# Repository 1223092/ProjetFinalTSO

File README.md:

## Project: Serrebrooke

### Logiciel
#### Comprend les dossiers des fichiers de programmation.

### Manuel Technique
#### Comprend le fichier texte explicant l'entièreté du projet.

### Materiel
#### Comprend de la documentation sur tous les objets physiques utilisé.

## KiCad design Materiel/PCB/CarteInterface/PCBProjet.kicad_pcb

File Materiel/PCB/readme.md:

# Schémas 
Répertoire qui contient fichiers KiCAD de la carte d'extension Serrebrooke.

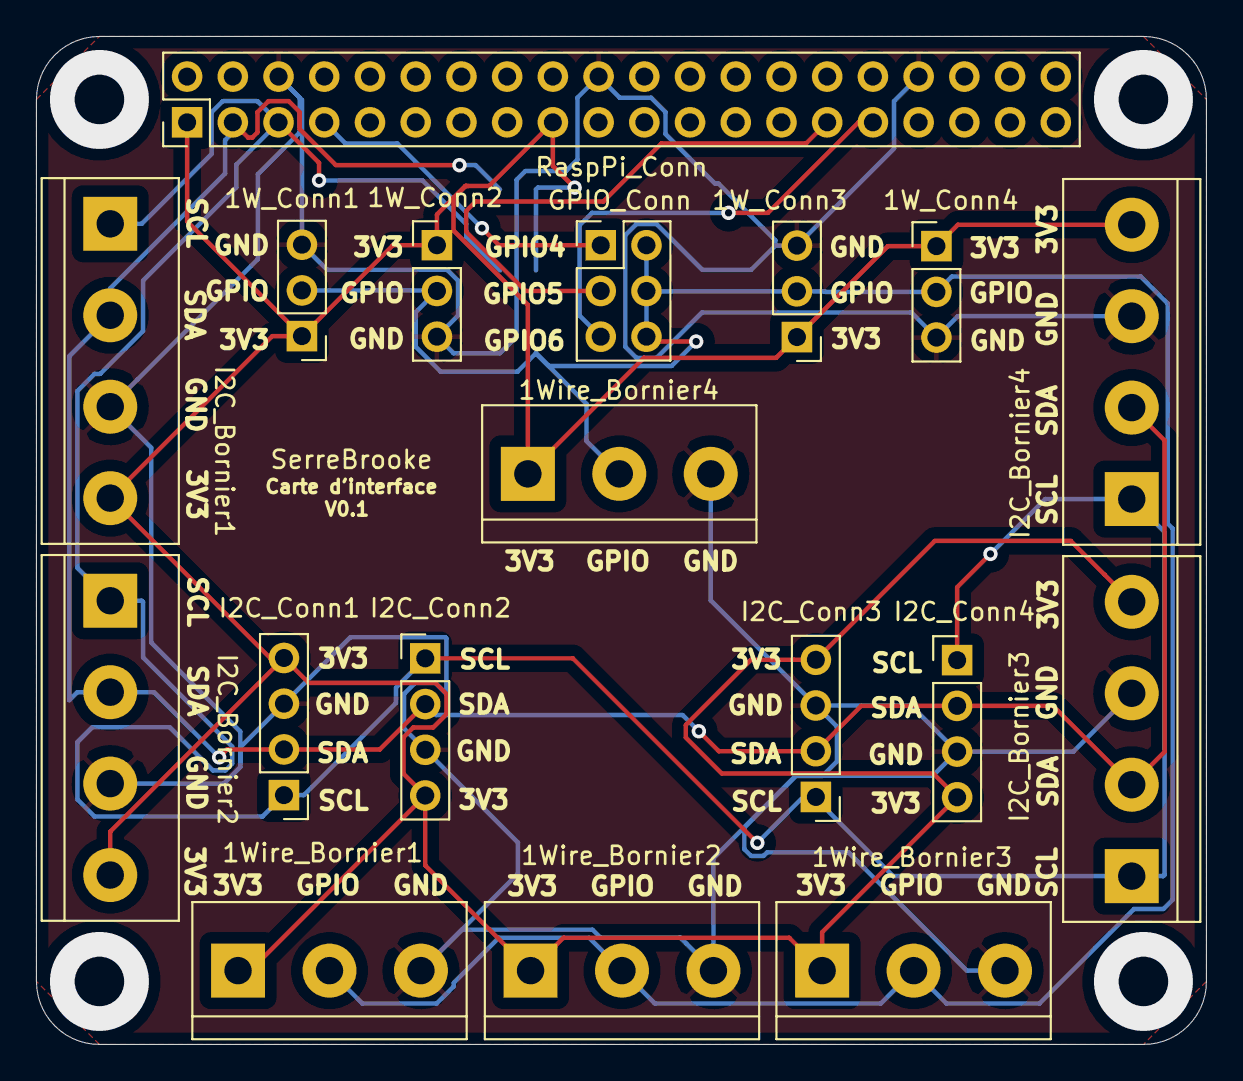
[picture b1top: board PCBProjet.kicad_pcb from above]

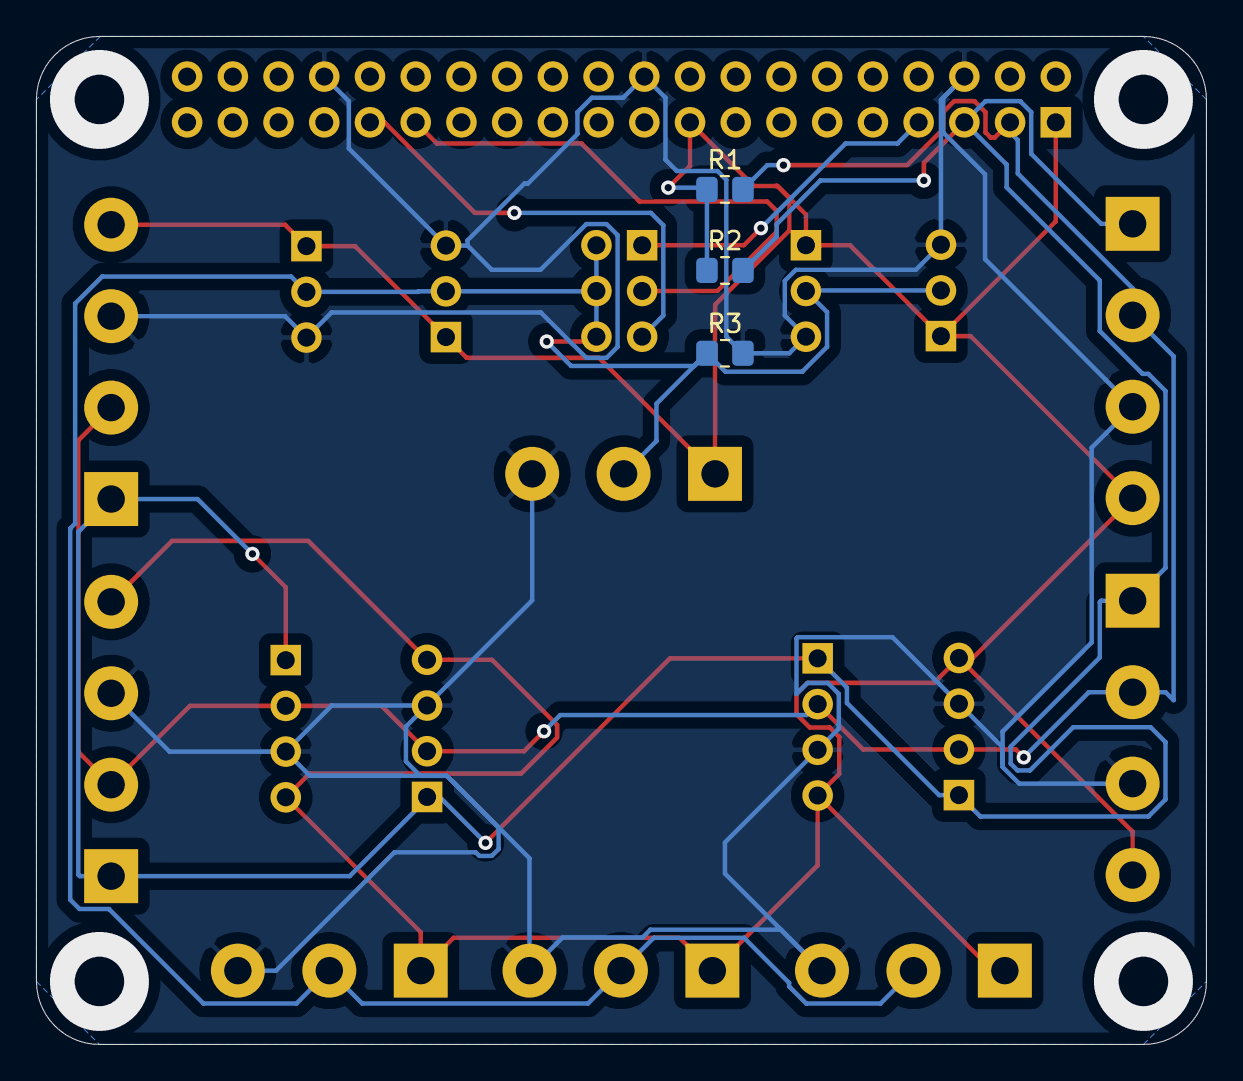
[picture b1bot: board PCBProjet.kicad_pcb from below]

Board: 2 copper layers, 65.0 x 56.0 mm, 21 parts (3 on the bottom side), 8 nets.

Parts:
1W_Conn1, 1W_Conn2, 1W_Conn3, 1W_Conn4: Conn_01x03; PinHeader_1x03_P2.54mm_Vertical
1Wire_Bornier1, 1Wire_Bornier2, 1Wire_Bornier3, 1Wire_Bornier4: Screw_Terminal_01x03; TerminalBlock_bornier-3_P5.08mm
GPIO_Conn: Conn_GPIO; PinHeader_2x03_P2.54mm_Vertical
I2C_Bornier1, I2C_Bornier2, I2C_Bornier3, I2C_Bornier4: Screw_Terminal_01x04; TerminalBlock_bornier-4_P5.08mm
I2C_Conn1, I2C_Conn2, I2C_Conn3, I2C_Conn4: Conn_01x04; PinHeader_1x04_P2.54mm_Vertical
R1, R2, R3: 4.7k; R_0805_2012Metric_Pad1.20x1.40mm_HandSolder
RaspPi_Conn: Raspberry_Pi_2_3; PinHeader_2x20_P2.54mm_Vertical

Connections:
/3V3: 1W_Conn1.1, 1W_Conn2.1, 1W_Conn3.1, 1W_Conn4.1, 1Wire_Bornier1.1, 1Wire_Bornier2.1, 1Wire_Bornier3.1, 1Wire_Bornier4.1, I2C_Bornier1.4, I2C_Bornier2.4, I2C_Bornier3.4, I2C_Bornier4.4, I2C_Conn1.4, I2C_Conn2.4, I2C_Conn3.4, I2C_Conn4.4, R1.1, R2.1, RaspPi_Conn.1, RaspPi_Conn.17
/GND: 1W_Conn1.3, 1W_Conn2.3, 1W_Conn3.3, 1W_Conn4.3, 1Wire_Bornier1.3, 1Wire_Bornier2.3, 1Wire_Bornier3.3, 1Wire_Bornier4.3, I2C_Bornier1.3, I2C_Bornier2.3, I2C_Bornier3.3, I2C_Bornier4.3, I2C_Conn1.3, I2C_Conn2.3, I2C_Conn3.3, I2C_Conn4.3, R3.2, RaspPi_Conn.6, RaspPi_Conn.20, RaspPi_Conn.34
/GPIO: 1W_Conn1.2, 1W_Conn2.2, 1W_Conn3.2, 1W_Conn4.2, 1Wire_Bornier1.2, 1Wire_Bornier2.2, 1Wire_Bornier3.2, 1Wire_Bornier4.2, GPIO_Conn.2, GPIO_Conn.4, GPIO_Conn.6, R3.1
/GPIO4: GPIO_Conn.1, RaspPi_Conn.7
/GPIO5: GPIO_Conn.3, RaspPi_Conn.29
/GPIO6: GPIO_Conn.5, RaspPi_Conn.31
/SCL: I2C_Bornier1.1, I2C_Bornier2.1, I2C_Bornier3.1, I2C_Bornier4.1, I2C_Conn1.1, I2C_Conn2.1, I2C_Conn3.1, I2C_Conn4.1, R2.2, RaspPi_Conn.5
/SDA: I2C_Bornier1.2, I2C_Bornier2.2, I2C_Bornier3.2, I2C_Bornier4.2, I2C_Conn1.2, I2C_Conn2.2, I2C_Conn3.2, I2C_Conn4.2, R1.2, RaspPi_Conn.3

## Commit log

2023-11-30 Release Balena
2023-12-19 Update Controle_GPIO.py
    RELEASE
    0.0.0+rev53
    avec boutons de Téléchargement de log: Trois boutons permettant de télécharger le journal des actions au format JSON, XML ou CSV.
2023-12-22 update du README
    ajout du brief de Controle_GPIO.py dans le README
2024-02-12 Test ordi Loic a Github
    One wire réglé.
    Enlevé les parties sur Hydroponie.
    Test interface écran physique.
2024-02-16 Les fichiers de configuration
    Les fichiers de configuration pour Docker et Balena.
    Changement fait pour avoir un point d'accès WIFI .
2024-02-28 Changement du nom du repo
    test changement nom
2024-02-28 Modification de l'arborescence
    test
2024-02-28 Ajout dossier manuel technique
    test1
2024-02-28 changer nom d'un dossier
    test1
2024-02-28 Mise à jour
    test1
2024-02-28 Travailler sur manuel technique
2024-03-13 Ajout affichage
    Ajout du status de connection sur interface
2024-03-13 temps d'acquisition
    changement pour le temps d'acquisition
2024-03-13 Update syst_interface.py
    Oublier d'importé syst_logique
2024-03-15 Affichage du status de connection
    L'écran affiche le status de connection : ON ou OFF
2024-03-18 nettoyage
    effacer les fichiers non necessaire
2024-03-18 version test du site
    version test du site de controle avec flask
2024-03-20 Delete du fichier boucle
    C'était un fichier de test
2024-03-20 Status de connection écran
2024-03-21 site
    nouveau site avec control et interface de programation .
    visuelment plus esthetique
2024-03-22 Update site.py
    ajout d'un sub tab pour programmation de valeurs fixes
2024-03-22 Update site.py
    css pour les text boxes de programmation de valeurs fixes
2024-03-22 Update getSensors_ds18b20.py
    changement pour avoir une tempMOY
2024-03-22 Update site.py
    fonction pour le boutton clear et set de temperature
2024-03-22 Update syst_interface.py
    fix affichage Temp. MOY
2024-04-03 Version présenstation
    version allégé pour la présentation 11 avril
2024-04-03 Mis à la bonne place
2024-04-05 documentation
2024-04-08 Manuel technique
    Description de l'échéancier.
    Grille des cours.
2024-04-10 réglage de bug sur le status de connexion
2024-04-18 Correction boucle de vérif statu connection
2024-04-19 Documentation
    Capteur d'humidité
2024-04-22 Manuel technique
    Procédure pour changer le logicel des prises intelligentes
2024-04-23 Site et boucles de control
    nouveau site et boucle de control
2024-04-26 coomit
2024-05-17 VERSION final crifa
    boucle de control est maintenant dans un thread dans syst_logique
    nouvelle version du site
2024-05-24 Disposition des libraries
2024-05-24 Refait les readme
2024-05-24 Nettoyage répertoire inutile
2024-05-27 Ajout de commentaire
2024-05-27 Amélioration présentation des fichiers de codes
2024-05-29 site split en 4 fichier
    site(site_final.py) utilise maintenant 3 autre fichiers (CSS,JAVASCRIPT,HTLM)
